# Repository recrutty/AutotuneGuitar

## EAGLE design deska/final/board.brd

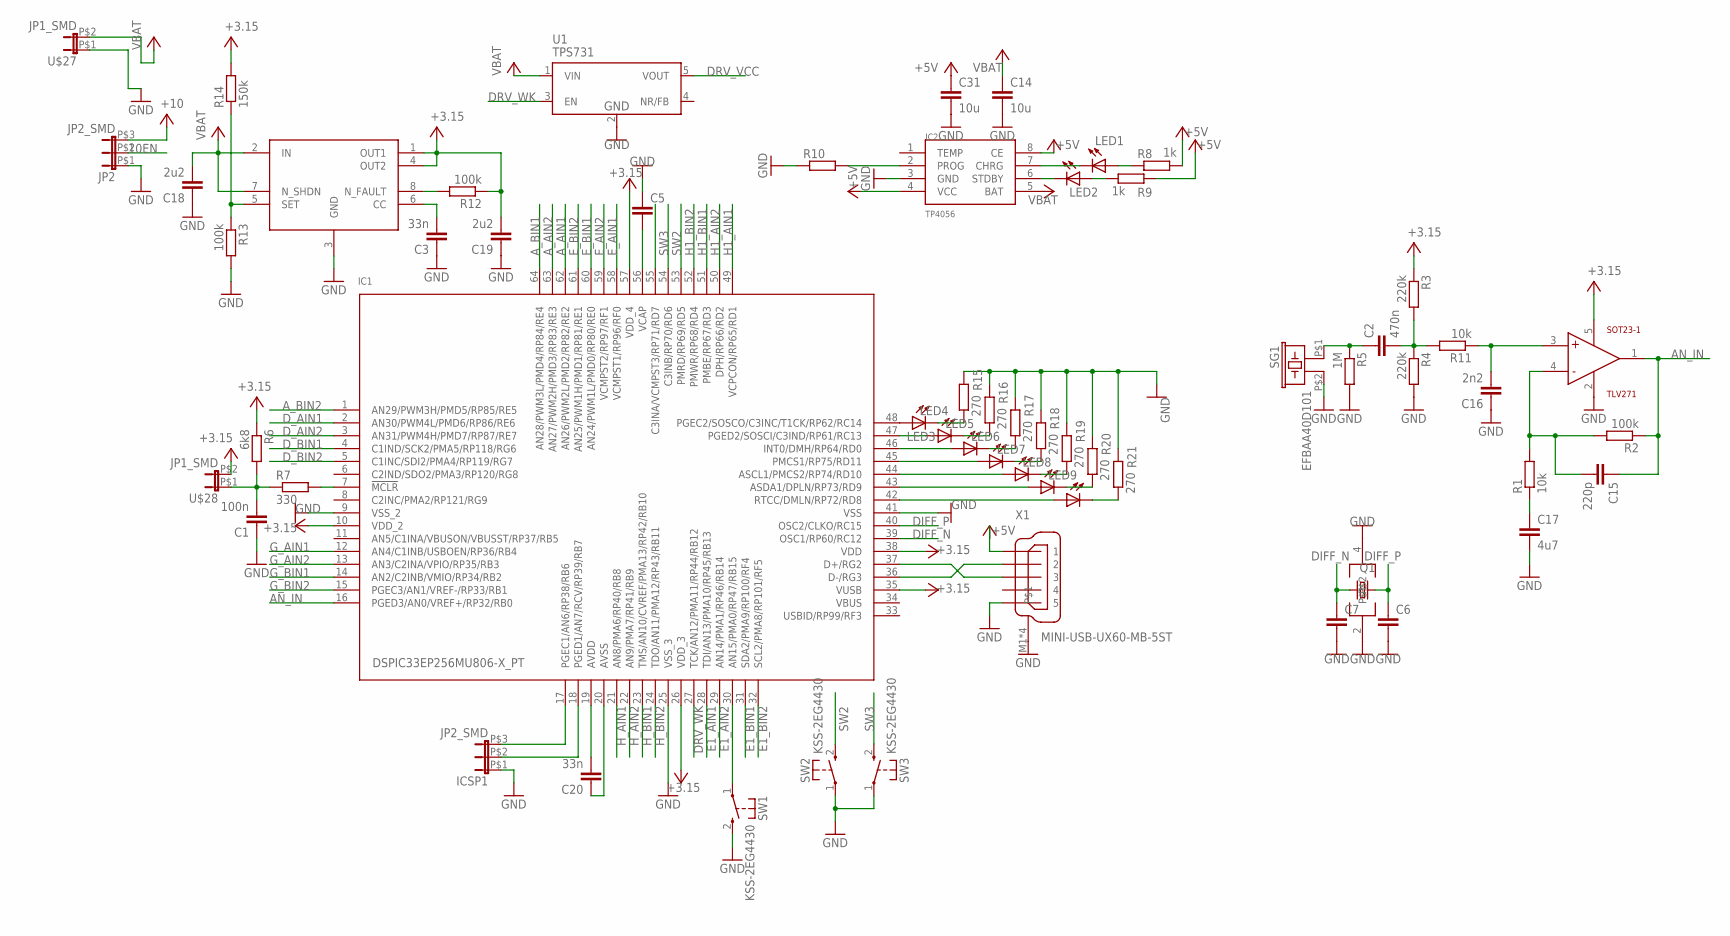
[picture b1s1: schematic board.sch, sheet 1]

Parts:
C1: 100n; C0603
C2: 470n; C0805
C3, C20: 33n; C0805
C5: CC1206; C1206
C6, C7: C; C0805
C14, C31: 10u; C1206
C15: 220p; C0805
C16: 2n2; C0805
C17: 4u7; C1206
C18, C19: 2u2; C0805
IC1: DSPIC33EP256MU806-X_PT; QFP64-10X10MC
IC2: TP4056; SOP-8
ICSP1: JP2_SMD
JP2: JP2_SMD
LED1, LED2, LED3, LED4, LED5, LED6, LED7, LED8, LED9: LED_ESML0603; LED_SML0603
Q1: CRYSTALCTS406; CTS406
R1, R11: 10k; R0805
R2, R12, R13: 100k; R0805
R3, R4: 220k; R0805
R5: 1M; R0805
R6: 6k8; R0603
R7: 330; R0603
R8, R9: 1k; R0805
R10: R; R0805
R14: 150k; R0805
R15, R16, R17, R18, R19, R20, R21: 270; R0805
SG1: EFBAA40D101
SOT23-1: TLV271; SOT23-5
SW1, SW2, SW3: KSS-2EG4430
U1: TPS731; SOT25
U$8: LP3982
U$27, U$28: JP1_SMD
X1: MINI-USB-UX60-MB-5ST; UX60-MB-5ST

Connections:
10EN: IC1.55 (C3INA/VCMPST3/RP71/RD7), JP2.P$2 (2)
+3.15: R6.1, U$28.P$2 (2)
+3.15V: C19.2, IC1.10 (VDD_2), IC1.26 (VDD_3), IC1.35 (VUSB), IC1.38 (VDD), IC1.57 (VDD_4), R3.1, R12.1, R14.2, SOT23-1.5 (VDD), U$8.1 (OUT1), U$8.4 (OUT2); also elsewhere on the board
+10V: JP2.P$3 (3); also elsewhere on the board
AN_IN: C15.1, IC1.16 (PGED3/AN0/VREF+/RP32/RB0), R2.1, SOT23-1.1 (OUT)
A_AIN1: IC1.62 (AN26/PWM2L/PMD2/RP82/RE2); also elsewhere on the board
A_AIN2: IC1.63 (AN27/PWM2H/PMD3/RP83/RE3); also elsewhere on the board
A_BIN1: IC1.64 (AN28/PWM3L/PMD4/RP84/RE4); also elsewhere on the board
A_BIN2: IC1.1 (AN29/PWM3H/PMD5/RP85/RE5); also elsewhere on the board
DIFF_N: C7.1, IC1.39 (OSC1/RP60/RC12), Q1.3 (2)
DIFF_NS: IC1.36 (D-/RG3), X1.2
DIFF_P: C6.1, IC1.40 (OSC2/CLKO/RC15), Q1.1
DIFF_PD: IC1.37 (D+/RG2), X1.3
DRV_VCC: U1.5 (VOUT); also elsewhere on the board
DRV_WK: IC1.27 (TCK/AN12/PMA11/RP44/RB12), U1.3 (EN)
D_AIN1: IC1.2 (AN30/PWM4L/PMD6/RP86/RE6); also elsewhere on the board
D_AIN2: IC1.3 (AN31/PWM4H/PMD7/RP87/RE7); also elsewhere on the board
D_BIN1: IC1.4 (C1IND/SCK2/PMA5/RP118/RG6); also elsewhere on the board
D_BIN2: IC1.5 (C1INC/SDI2/PMA4/RP119/RG7); also elsewhere on the board
E1_AIN1: IC1.28 (TDI/AN13/PMA10/RP45/RB13); also elsewhere on the board
E1_AIN2: IC1.29 (AN14/PMA1/RP46/RB14); also elsewhere on the board
E1_BIN1: IC1.31 (SDA2/PMA9/RP100/RF4); also elsewhere on the board
E1_BIN2: IC1.32 (SCL2/PMA8/RP101/RF5); also elsewhere on the board
E_AIN1: IC1.58 (VCMPST1/RP96/RF0); also elsewhere on the board
E_AIN2: IC1.59 (VCMPST2/RP97/RF1); also elsewhere on the board
E_BIN1: IC1.60 (AN24/PWM1L/PMD0/RP80/RE0); also elsewhere on the board
E_BIN2: IC1.61 (AN25/PWM1H/PMD1/RP81/RE1); also elsewhere on the board
FGH: IC1.17 (PGEC1/AN6/RP38/RB6), ICSP1.P$3 (3)
GFD: IC1.18 (PGED1/AN7/RCV/RP39/RB7), ICSP1.P$2 (2)
GND: C1.1, C3.1, C5.1, C6.2, C7.2, C14.2, C16.1, C17.2, C18.1, C19.1, C31.2, IC1.9 (VSS_2), IC1.25 (VSS_3), IC1.41 (VSS), IC2.3 (GND), ICSP1.P$1 (1), JP2.P$1 (1), Q1.2, Q1.4, R4.2, R5.2, R10.1, R13.2, R15.2, R16.2, R17.2, R18.2, R19.2, R20.2, R21.2, SG1.P$2 (2), SOT23-1.2 (GND), SW1.2 (S), SW2.1, SW3.1, U1.2 (GND), U$8.3 (GND), U$27.P$1 (1), X1.5, X1.M1, X1.M2, X1.M3, X1.M4; also elsewhere on the board
G_AIN1: IC1.12 (AN4/C1INB/USBOEN/RP36/RB4); also elsewhere on the board
G_AIN2: IC1.13 (AN3/C2INA/VPIO/RP35/RB3); also elsewhere on the board
G_BIN1: IC1.14 (AN2/C2INB/VMIO/RP34/RB2); also elsewhere on the board
G_BIN2: IC1.15 (PGEC3/AN1/VREF-/RP33/RB1); also elsewhere on the board
H1_AIN1: IC1.49 (VCPCON/RP65/RD1); also elsewhere on the board
H1_AIN2: IC1.50 (DPH/RP66/RD2); also elsewhere on the board
H1_BIN1: IC1.51 (PMBE/RP67/RD3); also elsewhere on the board
H1_BIN2: IC1.52 (PMWR/RP68/RD4); also elsewhere on the board
H_AIN1: IC1.21 (AN8/PMA6/RP40/RB8); also elsewhere on the board
H_AIN2: IC1.22 (AN9/PMA7/RP41/RB9); also elsewhere on the board
H_BIN1: IC1.23 (TMS/AN10/CVREF/PMA13/RP42/RB10); also elsewhere on the board
H_BIN2: IC1.24 (TDO/AN11/PMA12/RP43/RB11); also elsewhere on the board
unnamed: C20.2, IC1.19 (AVDD)
unnamed: C20.1, IC1.20 (AVSS)
unnamed: IC1.7 (!MCLR), R7.2
unnamed: C5.2, IC1.56 (VCAP)
unnamed: IC1.48 (PGEC2/SOSCO/C3INC/T1CK/RP62/RC14), LED3.A
unnamed: C15.2, R1.2, R2.2, SOT23-1.4 (IN-)
unnamed: C17.1, R1.1
unnamed: C2.2, R3.2, R4.1, R11.2
unnamed: IC2.7 (CHRG), LED1.C
unnamed: C2.1, R5.1, SG1.P$1 (1)
unnamed: IC2.6 (STDBY), LED2.C
unnamed: LED2.A, R9.1
unnamed: LED1.A, R8.1
unnamed: IC2.2 (PROG), R10.2
unnamed: C16.2, R11.1, SOT23-1.3 (IN+)
unnamed: R12.2, U$8.8 (N_FAULT)
unnamed: C3.2, U$8.6 (CC)
unnamed: IC1.47 (PGED2/SOSCI/C3IND/RP61/RC13), LED4.A
unnamed: R13.1, R14.1, U$8.5 (SET)
unnamed: IC1.46 (INT0/DMH/RP64/RD0), LED5.A
unnamed: IC1.45 (PMCS1/RP75/RD11), LED6.A
unnamed: IC1.44 (ASCL1/PMCS2/RP74/RD10), LED7.A
unnamed: IC1.43 (ASDA1/DPLN/RP73/RD9), LED8.A
unnamed: IC1.42 (RTCC/DMLN/RP72/RD8), LED9.A
unnamed: LED9.C, R21.1
unnamed: LED8.C, R20.1
unnamed: LED7.C, R19.1
unnamed: LED6.C, R18.1
unnamed: LED5.C, R17.1
unnamed: LED4.C, R16.1
unnamed: LED3.C, R15.1
unnamed: IC1.30 (AN15/PMA0/RP47/RB15), SW1.1
RST: C1.2, R6.2, R7.1, U$28.P$1 (1)
SW2: IC1.53 (PMRD/RP69/RD5), SW2.2 (S)
SW3: IC1.54 (C3INB/RP70/RD6), SW3.2 (S)
VBAT: C14.1, C18.2, IC1.11 (AN5/C1INA/VBUSON/VBUSST/RP37/RB5), IC2.5 (BAT), U1.1 (VIN), U$8.2 (IN), U$8.7 (N_SHDN), U$27.P$2 (2); also elsewhere on the board
VBUS: IC1.34 (VBUS)

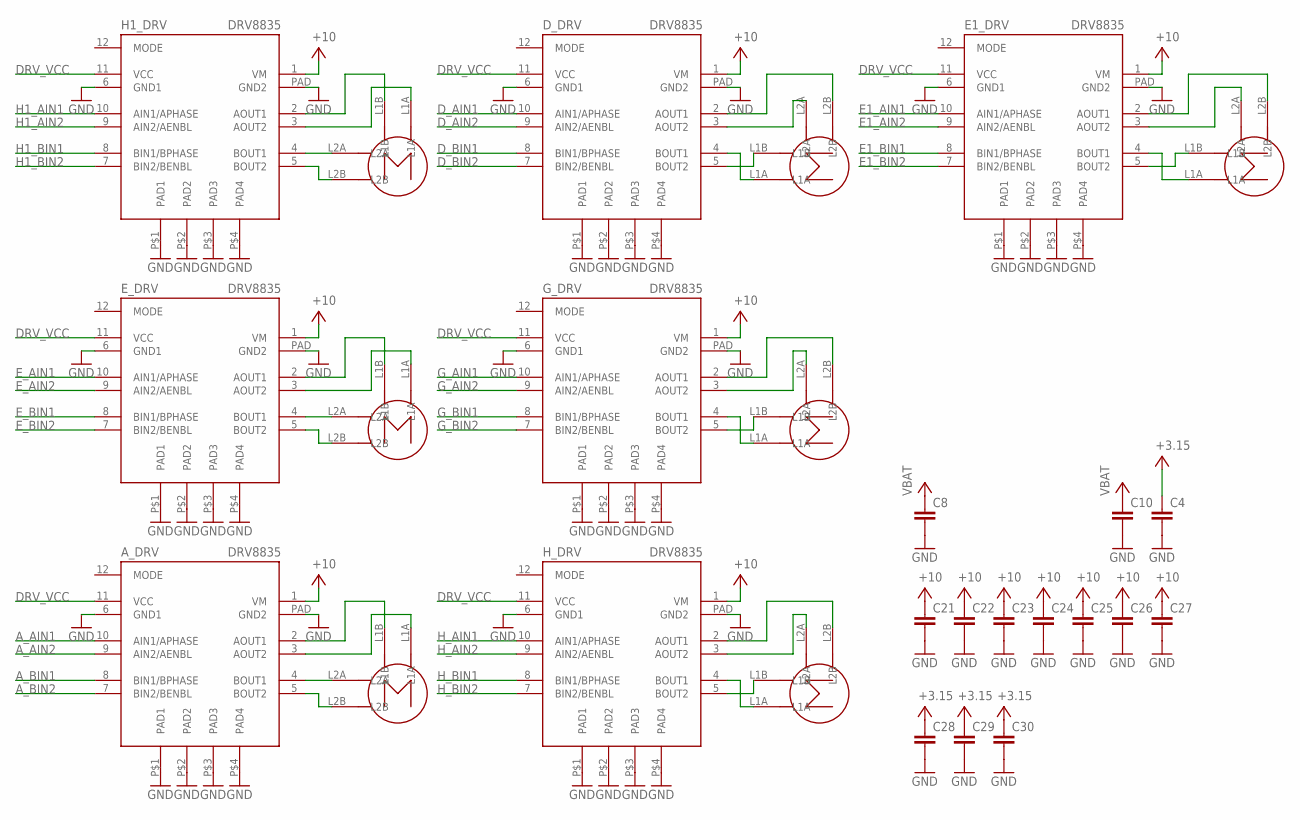
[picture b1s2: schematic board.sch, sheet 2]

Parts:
A_DRV: DRV8835; WSON_2X3
C4, C8, C10, C21, C22, C23, C24, C25, C26, C27, C28, C29, C30: CC1206; C1206
D_DRV: DRV8835; WSON_2X3
E1_DRV: DRV8835; WSON_2X3
E_DRV: DRV8835; WSON_2X3
G_DRV: DRV8835; WSON_2X3
H1_DRV: DRV8835; WSON_2X3
H1šWF: H1; STEP_MOTOR
H_DRV: DRV8835; WSON_2X3
U$1, U$2, U$3, U$7: STEP_MOTOR_MIRROR
U$4, U$6: STEP_MOTOR

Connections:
+3.15V: C4.1, C28.1, C29.1, C30.1; also elsewhere on the board
+10V: A_DRV.1 (VM), C21.1, C22.1, C23.1, C24.1, C25.1, C26.1, C27.1, D_DRV.1 (VM), E1_DRV.1 (VM), E_DRV.1 (VM), G_DRV.1 (VM), H1_DRV.1 (VM), H_DRV.1 (VM); also elsewhere on the board
A_AIN1: A_DRV.10 (AIN1/APHASE); also elsewhere on the board
A_AIN2: A_DRV.9 (AIN2/AENBL); also elsewhere on the board
A_BIN1: A_DRV.8 (BIN1/BPHASE); also elsewhere on the board
A_BIN2: A_DRV.7 (BIN2/BENBL); also elsewhere on the board
DRV_VCC: A_DRV.11 (VCC), D_DRV.11 (VCC), E1_DRV.11 (VCC), E_DRV.11 (VCC), G_DRV.11 (VCC), H1_DRV.11 (VCC), H_DRV.11 (VCC); also elsewhere on the board
D_AIN1: D_DRV.10 (AIN1/APHASE); also elsewhere on the board
D_AIN2: D_DRV.9 (AIN2/AENBL); also elsewhere on the board
D_BIN1: D_DRV.8 (BIN1/BPHASE); also elsewhere on the board
D_BIN2: D_DRV.7 (BIN2/BENBL); also elsewhere on the board
E1_AIN1: E1_DRV.10 (AIN1/APHASE); also elsewhere on the board
E1_AIN2: E1_DRV.9 (AIN2/AENBL); also elsewhere on the board
E1_BIN1: E1_DRV.8 (BIN1/BPHASE); also elsewhere on the board
E1_BIN2: E1_DRV.7 (BIN2/BENBL); also elsewhere on the board
E_AIN1: E_DRV.10 (AIN1/APHASE); also elsewhere on the board
E_AIN2: E_DRV.9 (AIN2/AENBL); also elsewhere on the board
E_BIN1: E_DRV.8 (BIN1/BPHASE); also elsewhere on the board
E_BIN2: E_DRV.7 (BIN2/BENBL); also elsewhere on the board
GND: A_DRV.6 (GND1), A_DRV.P$1 (PAD1), A_DRV.P$2 (PAD2), A_DRV.P$3 (PAD3), A_DRV.P$4 (PAD4), A_DRV.PAD (GND2), C4.2, C8.2, C10.2, C21.2, C22.2, C23.2, C24.2, C25.2, C26.2, C27.2, C28.2, C29.2, C30.2, D_DRV.6 (GND1), D_DRV.P$1 (PAD1), D_DRV.P$2 (PAD2), D_DRV.P$3 (PAD3), D_DRV.P$4 (PAD4), D_DRV.PAD (GND2), E1_DRV.6 (GND1), E1_DRV.P$1 (PAD1), E1_DRV.P$2 (PAD2), E1_DRV.P$3 (PAD3), E1_DRV.P$4 (PAD4), E1_DRV.PAD (GND2), E_DRV.6 (GND1), E_DRV.P$1 (PAD1), E_DRV.P$2 (PAD2), E_DRV.P$3 (PAD3), E_DRV.P$4 (PAD4), E_DRV.PAD (GND2), G_DRV.6 (GND1), G_DRV.P$1 (PAD1), G_DRV.P$2 (PAD2), G_DRV.P$3 (PAD3), G_DRV.P$4 (PAD4), G_DRV.PAD (GND2), H1_DRV.6 (GND1), H1_DRV.P$1 (PAD1), H1_DRV.P$2 (PAD2), H1_DRV.P$3 (PAD3), H1_DRV.P$4 (PAD4), H1_DRV.PAD (GND2), H_DRV.6 (GND1), H_DRV.P$1 (PAD1), H_DRV.P$2 (PAD2), H_DRV.P$3 (PAD3), H_DRV.P$4 (PAD4), H_DRV.PAD (GND2); also elsewhere on the board
G_AIN1: G_DRV.10 (AIN1/APHASE); also elsewhere on the board
G_AIN2: G_DRV.9 (AIN2/AENBL); also elsewhere on the board
G_BIN1: G_DRV.8 (BIN1/BPHASE); also elsewhere on the board
G_BIN2: G_DRV.7 (BIN2/BENBL); also elsewhere on the board
H1_AIN1: H1_DRV.10 (AIN1/APHASE); also elsewhere on the board
H1_AIN2: H1_DRV.9 (AIN2/AENBL); also elsewhere on the board
H1_BIN1: H1_DRV.8 (BIN1/BPHASE); also elsewhere on the board
H1_BIN2: H1_DRV.7 (BIN2/BENBL); also elsewhere on the board
H_AIN1: H_DRV.10 (AIN1/APHASE); also elsewhere on the board
H_AIN2: H_DRV.9 (AIN2/AENBL); also elsewhere on the board
H_BIN1: H_DRV.8 (BIN1/BPHASE); also elsewhere on the board
H_BIN2: H_DRV.7 (BIN2/BENBL); also elsewhere on the board
unnamed: D_DRV.2 (AOUT1), U$2.L2B
unnamed: D_DRV.3 (AOUT2), U$2.L2A
unnamed: D_DRV.5 (BOUT2), U$2.L1B
unnamed: D_DRV.4 (BOUT1), U$2.L1A
unnamed: E1_DRV.2 (AOUT1), U$1.L2B
unnamed: E1_DRV.3 (AOUT2), U$1.L2A
unnamed: E1_DRV.4 (BOUT1), U$1.L1A
unnamed: E1_DRV.5 (BOUT2), U$1.L1B
unnamed: G_DRV.2 (AOUT1), U$3.L2B
unnamed: G_DRV.3 (AOUT2), U$3.L2A
unnamed: G_DRV.5 (BOUT2), U$3.L1B
unnamed: G_DRV.4 (BOUT1), U$3.L1A
unnamed: E_DRV.5 (BOUT2), U$4.L2B
unnamed: H_DRV.4 (BOUT1), U$7.L1A
unnamed: E_DRV.2 (AOUT1), U$4.L1B
unnamed: E_DRV.3 (AOUT2), U$4.L1A
unnamed: E_DRV.4 (BOUT1), U$4.L2A
unnamed: A_DRV.5 (BOUT2), U$6.L2B
unnamed: H1_DRV.2 (AOUT1), H1šWF.L1B
unnamed: H1_DRV.3 (AOUT2), H1šWF.L1A
unnamed: H1_DRV.5 (BOUT2), H1šWF.L2B
unnamed: H1_DRV.4 (BOUT1), H1šWF.L2A
unnamed: A_DRV.2 (AOUT1), U$6.L1B
unnamed: A_DRV.3 (AOUT2), U$6.L1A
unnamed: A_DRV.4 (BOUT1), U$6.L2A
unnamed: H_DRV.2 (AOUT1), U$7.L2B
unnamed: H_DRV.3 (AOUT2), U$7.L2A
unnamed: H_DRV.5 (BOUT2), U$7.L1B
VBAT: C8.1, C10.1; also elsewhere on the board

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
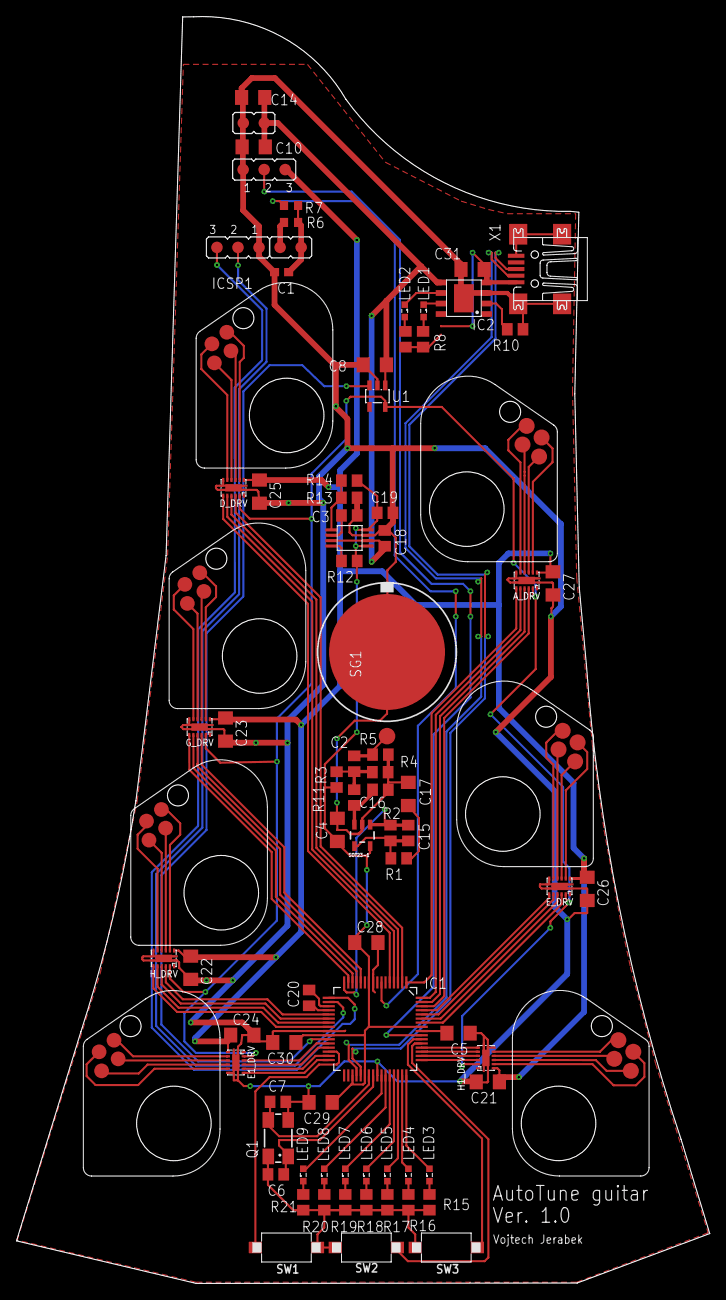
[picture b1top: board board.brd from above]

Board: 2 copper layers, 83.7 x 153.0 mm, 86 parts (0 on the bottom side), 108 nets.

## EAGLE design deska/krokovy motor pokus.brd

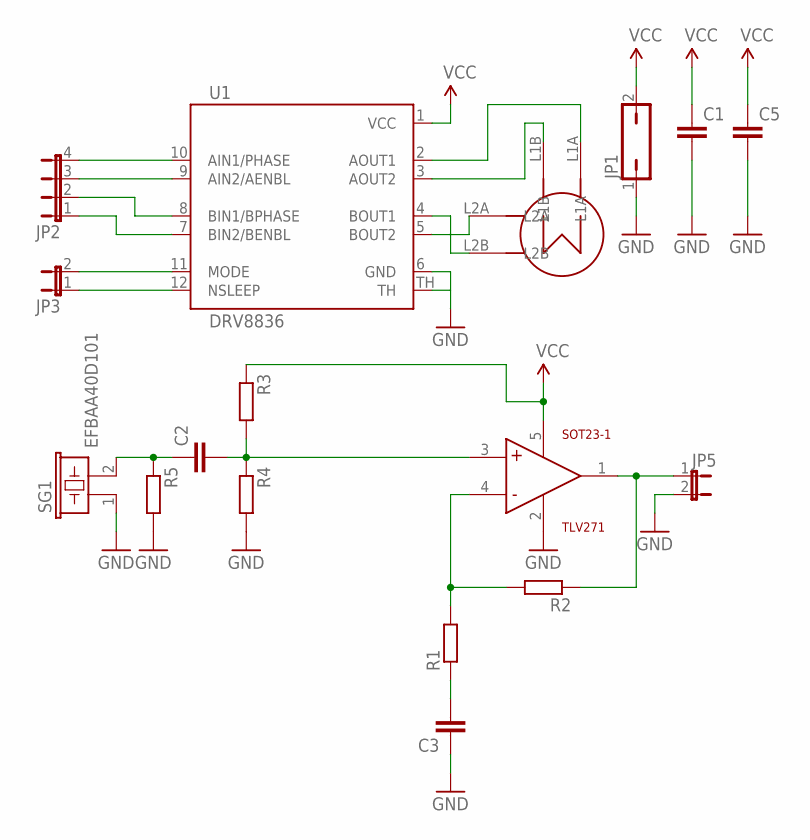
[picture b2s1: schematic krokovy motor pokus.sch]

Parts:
C1, C2, C3, C5: CC1206; C1206
JP1: JP1Q; JP1
JP2: JP4E; JP4
JP3, JP5: JP1E; JP1
R1, R2, R3, R4, R5: RR1206; R1206
SG1: EFBAA40D101
SOT23-1: TLV271; SOT23-5
U1: DRV8836; 12WSON
U$1: STEP_MOTOR

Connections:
GND: C1.2, C3.1, C5.2, JP1.1, JP5.2, R4.2, R5.2, SG1.1, SOT23-1.2 (GND), U1.6 (GND), U1.TH
unnamed: JP2.4, U1.10 (AIN1/PHASE)
unnamed: JP2.3, U1.9 (AIN2/AENBL)
unnamed: JP2.2, U1.8 (BIN1/BPHASE)
unnamed: JP2.1, U1.7 (BIN2/BENBL)
unnamed: JP3.1, U1.12 (NSLEEP)
unnamed: JP3.2, U1.11 (MODE)
unnamed: U1.2 (AOUT1), U$1.L1A
unnamed: U1.3 (AOUT2), U$1.L1B
unnamed: U1.5 (BOUT2), U$1.L2A
unnamed: U1.4 (BOUT1), U$1.L2B
unnamed: JP5.1, R2.1, SOT23-1.1 (OUT)
unnamed: R1.2, R2.2, SOT23-1.4 (IN-)
unnamed: C3.2, R1.1
unnamed: C2.2, R3.2, R4.1, SOT23-1.3 (IN+)
unnamed: C2.1, R5.1, SG1.2
VCC: C1.1, C5.1, JP1.2, R3.1, SOT23-1.5 (VDD), U1.1 (VCC)

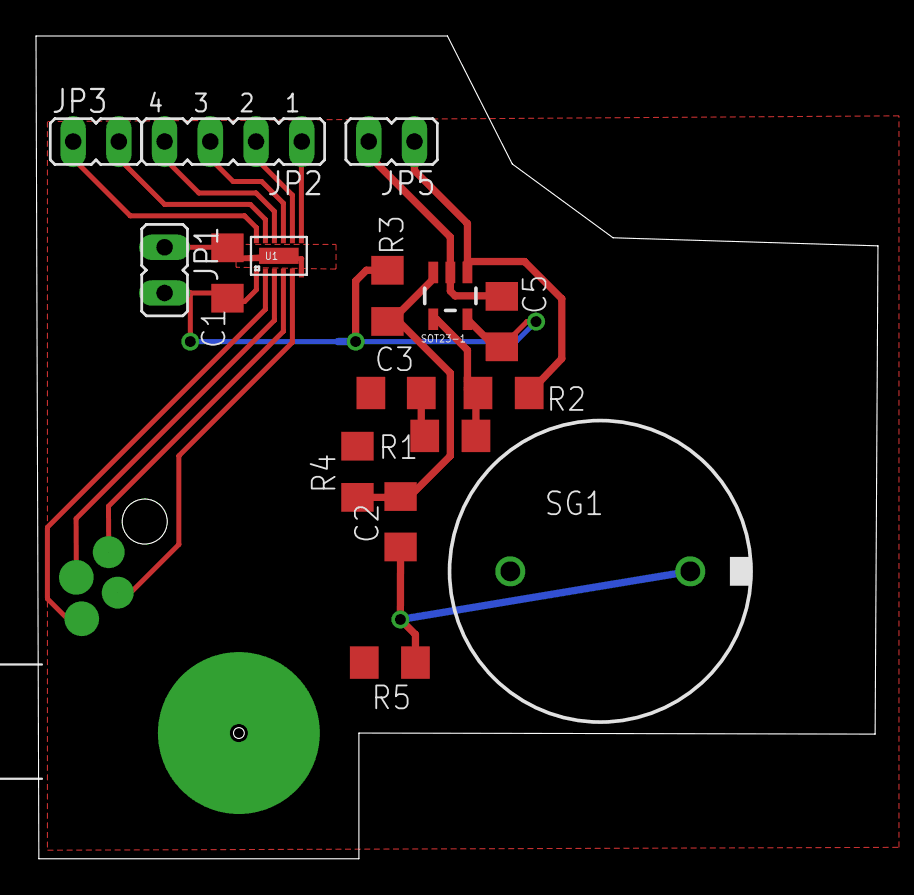
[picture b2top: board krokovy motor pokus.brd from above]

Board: 2 copper layers, 46.8 x 45.7 mm, 17 parts (0 on the bottom side), 17 nets.

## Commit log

2017-02-20 adding motors
2017-02-22 adding docs
2017-02-22 better step motor, add ADC
2017-02-26 testing sw
2017-02-27 doplneno spojeni avdd a vdd
2017-02-27 vdd prog
2017-02-27 adding pins change leds structure
2017-02-27 deleting leds
2017-02-27 Rename leds.h to Leds.h
2017-02-28 drivers testing
2017-03-01 dostep
2017-03-02 All motors test SW
2017-03-02 add leds
2017-03-03 completed SW
2017-03-06 high clk, high ADC
2017-03-07 mereni strun zaklad
2017-03-09 5 strun ladi dobre. hluboke maj problem
2017-03-09 vetsi klouzavy prumer
2017-03-09 mereni h struny
2017-03-13 pridan eeict
2017-03-20 hrani s FFT. jeste nejede
2017-03-26 fft mereni
2017-03-29 zacatek vyhodnoceni fft
2017-04-04 mereni fft
2017-04-17 SW pro prezentovani
2017-04-20 psani diplomky
2017-04-21 psani v praci
2017-04-23 pridana prezentace
2017-04-23 doplneni priloh
2017-05-07 psani HW
2017-05-10 Added Untitled Diagram.xml
2017-05-10 dalsi psani
2017-05-14 psani dal
2017-05-17 prvni verze
2017-05-19 oprava pravopisu
2017-05-21 Added StepMotor.xml
2017-05-21 Added StepMotor.pdf
2017-05-21 tuninning po kritice
2017-05-21 jojo
2017-05-21 aerghqefh
    egw
2017-05-21 Added analyza.xml
2017-05-21 Added analyza.pdf
2017-05-21 pulka je po revizi
2017-05-21 tata rewiew
2017-05-22 dalsi verze
2017-05-23 pripraveno k tisku
2017-06-04 prezentace

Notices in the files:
parts and their libraries:
SparkFun-Aesthetics: Licensing: Creative Commons ShareAlike 4.0 International - https://creativecommons.org/licenses/by-sa/4.0
